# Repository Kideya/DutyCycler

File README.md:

# DutyCycler
A  lightweight PWM light dimmer designed for smooth brightness control. Tame your LEDs, shift the shades, and fade like a pro — whether you need a subtle glow or full party mode. Built for makers, hackers, and anyone who thinks "maximum brightness" is overrated.

- Generated with ChatGPT

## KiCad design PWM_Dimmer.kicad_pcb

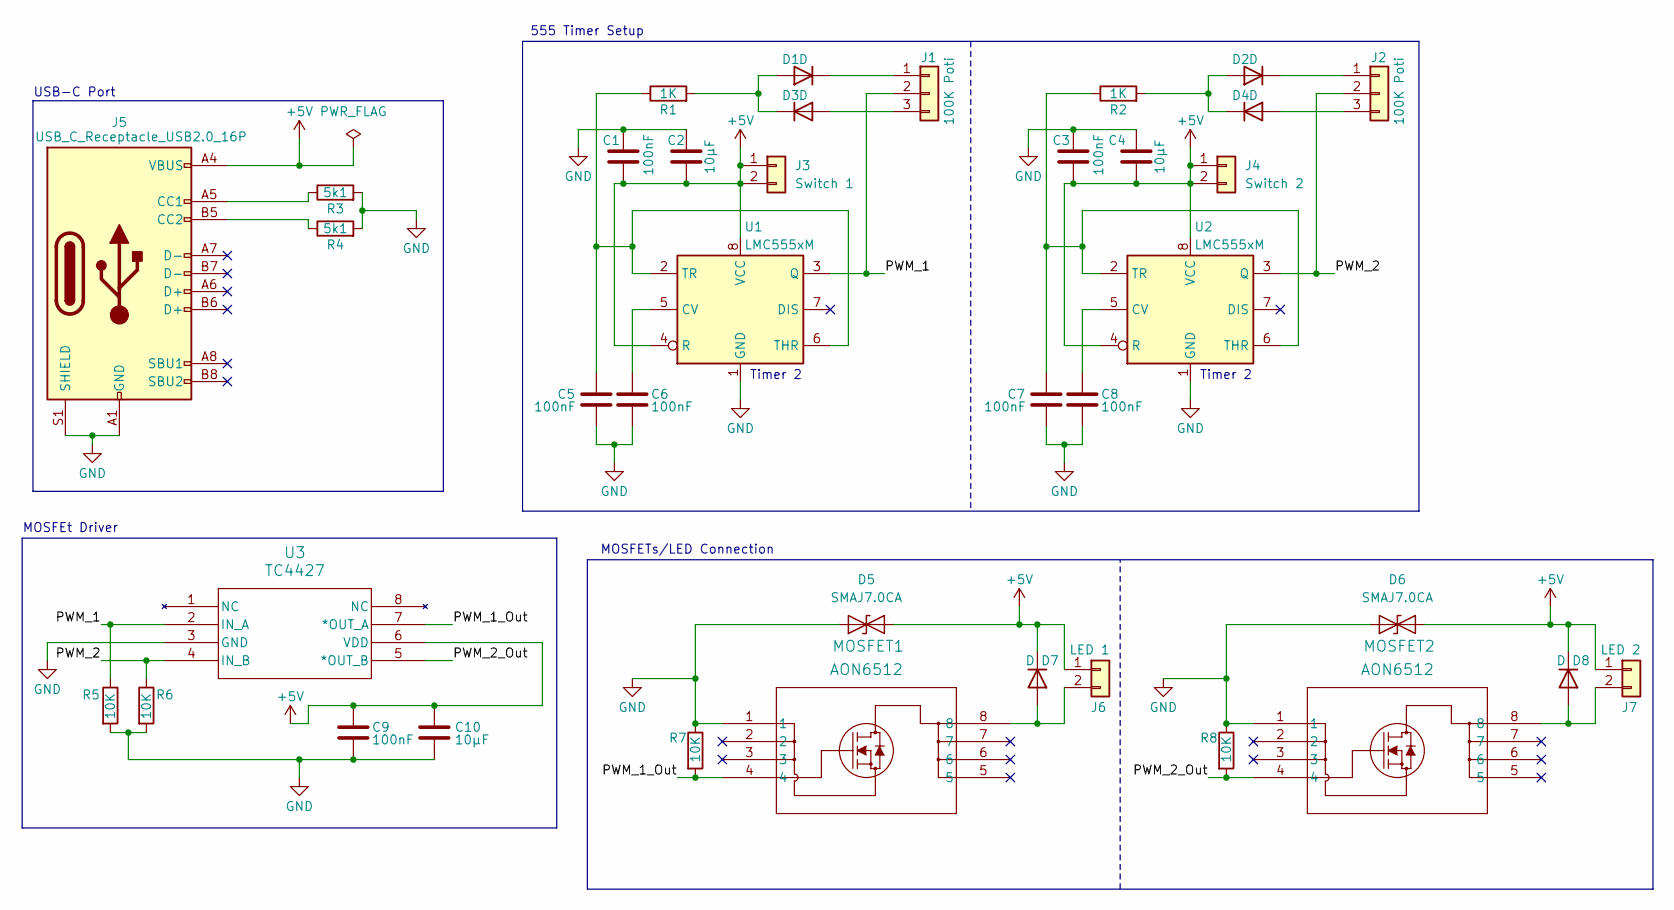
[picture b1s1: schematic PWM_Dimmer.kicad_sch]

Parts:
C1, C3, C5, C6, C7, C8, C9: 100nF; R_0603_1608Metric_Pad0.98x0.95mm_HandSolder
C2, C4, C10: 10µF; R_0603_1608Metric_Pad0.98x0.95mm_HandSolder
D1, D2, D3, D4, D7, D8: D; D_0603_1608Metric_Pad1.05x0.95mm_HandSolder
D5, D6: SMAJ7.0CA; D_SMB_Handsoldering
J1, J2: 100K Poti; PinHeader_1x03_P2.54mm_Vertical
J3: Switch 1; PinHeader_1x02_P2.54mm_Vertical
J4: Switch 2; PinHeader_1x02_P2.54mm_Vertical
J5: USB_C_Receptacle_USB2.0_16P; USB_C_Receptacle_Palconn_UTC16-G
J6: LED 1; Molex_PicoBlade_53047-0210_1x02_P1.25mm_Vertical
J7: LED 2; Molex_PicoBlade_53047-0210_1x02_P1.25mm_Vertical
MOSFET1, MOSFET2: AON6512; DFN5X6_8L_EP1_P_AOS
R1, R2: 1K; R_0603_1608Metric_Pad0.98x0.95mm_HandSolder
R3, R4: 5k1; R_0603_1608Metric_Pad0.98x0.95mm_HandSolder
R5, R6, R7, R8: 10K; R_0603_1608Metric_Pad0.98x0.95mm_HandSolder
U1, U2: LMC555xM; SOIC-8_3.9x4.9mm_P1.27mm
U3: TC4427; SOIC8-N_MC_MCH

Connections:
+5V: C1.2, C2.2, C3.2, C4.2, C9.1, C10.1, D5.1 (A1), D6.1 (A1), D7.1 (K), D8.1 (K), J3.1, J3.2, J4.1, J4.2, J5.A4 (VBUS), J5.A9 (VBUS), J5.B4 (VBUS), J5.B9 (VBUS), J6.1, J7.1, U1.4 (R), U1.8 (VCC), U2.4 (R), U2.8 (VCC), U3.6 (VDD)
/PWM_1: J1.2, R5.1, U1.3 (Q), U3.2 (IN_A)
/PWM_1_Out: MOSFET1.4, R7.2, U3.7 (*OUT_A)
/PWM_2: J2.2, R6.1, U2.3 (Q), U3.4 (IN_B)
/PWM_2_Out: MOSFET2.4, R8.2, U3.5 (*OUT_B)
GND: C1.1, C2.1, C3.1, C4.1, C5.2, C6.2, C7.2, C8.2, C9.2, C10.2, D5.2 (A2), D6.2 (A2), J5.A1 (GND), J5.A12 (GND), J5.B1 (GND), J5.B12 (GND), J5.S1 (SHIELD), MOSFET1.1, MOSFET2.1, R3.2, R4.2, R5.2, R6.2, R7.1, R8.1, U1.1 (GND), U2.1 (GND), U3.3 (GND)
unnamed: D1.2 (A), D3.1 (K), R1.2
unnamed: D1.1 (K), J1.1
unnamed: D2.2 (A), D4.1 (K), R2.2
unnamed: D2.1 (K), J2.1
unnamed: D3.2 (A), J1.3
unnamed: D4.2 (A), J2.3
unnamed: D7.2 (A), J6.2, MOSFET1.8
unnamed: D8.2 (A), J7.2, MOSFET2.8
unnamed: J5.A5 (CC1), R3.1
unnamed: J5.B5 (CC2), R4.1
unnamed: C6.1, U1.5 (CV)
unnamed: C5.1, R1.1, U1.2 (TR), U1.6 (THR)
unnamed: C8.1, U2.5 (CV)
unnamed: C7.1, R2.1, U2.2 (TR), U2.6 (THR)

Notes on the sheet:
555 Timer Setup
MOSFEt Driver
USB-C Port
Timer 2
MOSFETs/LED Connection

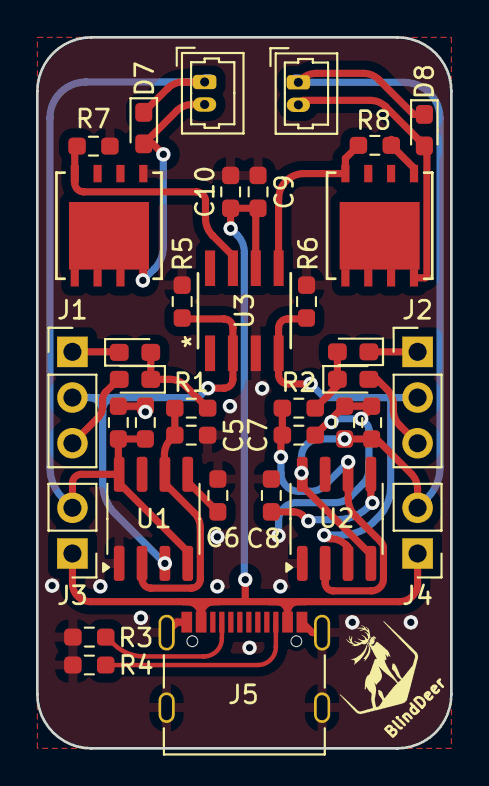
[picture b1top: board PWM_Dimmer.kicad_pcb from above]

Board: 2 copper layers, 23.0 x 39.5 mm, 36 parts (0 on the bottom side), 20 nets.

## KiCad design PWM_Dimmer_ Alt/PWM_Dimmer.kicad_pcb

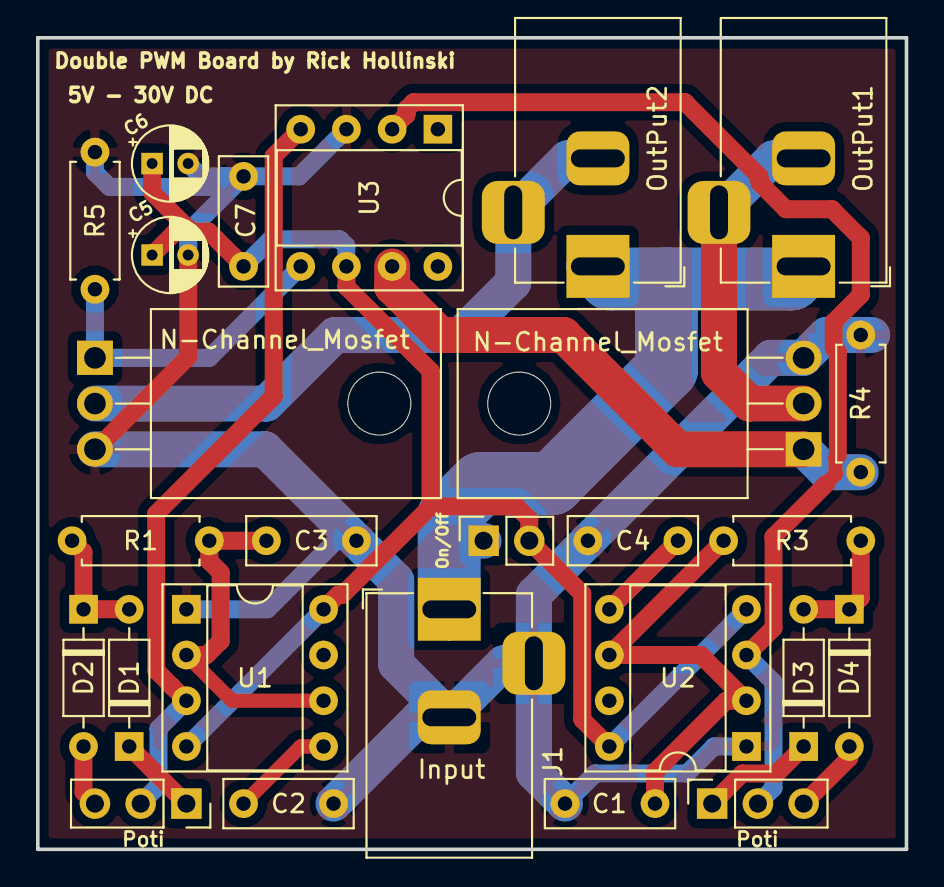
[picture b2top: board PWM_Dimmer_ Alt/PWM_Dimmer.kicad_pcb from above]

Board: 2 copper layers, 48.3 x 45.1 mm, 26 parts (0 on the bottom side), 19 nets.

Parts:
C1, C2, C3, C4, C7: 100n; C_Disc_D7.0mm_W2.5mm_P5.00mm
C5, C6: 10µ; CP_Radial_D4.0mm_P2.00mm
D1, D2, D3, D4: D; D_DO-35_SOD27_P7.62mm_Horizontal
J1: Input; BarrelJack_Horizontal
J2, J3: Poti; PinSocket_1x03_P2.54mm_Vertical
J4: OutPut1; BarrelJack_Horizontal
J5: OutPut2; BarrelJack_Horizontal
J6: On/Off; PinSocket_1x02_P2.54mm_Vertical
Q2, Q3: N-Channel_Mosfet; TO-220F-3_Horizontal_TabDown
R1, R3, R4, R5: 10K; R_Axial_DIN0207_L6.3mm_D2.5mm_P7.62mm_Horizontal
U1, U2: LMC555xN; DIP-8_W7.62mm_Socket
U3: TC4426CPA; DIP-8_W7.62mm_Socket

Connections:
+12V: J1.1, J4.1, J5.1, J6.1
GND: C1.2, C2.2, C3.2, C4.2, C5.2, C6.2, C7.2, J1.2, J1.3, Q2.3, Q3.3, R4.2, R5.2, U1.1, U2.1, U3.3
unnamed: C1.1, R3.2, U2.2, U2.6
unnamed: C2.1, U1.5
unnamed: C3.1, R1.2, U1.2, U1.6
unnamed: C4.1, U2.5
unnamed: D1.1, J2.1
unnamed: D1.2, D2.1, R1.1
unnamed: D2.2, J2.3
unnamed: D3.1, J3.1
unnamed: D3.2, D4.1, R3.1
unnamed: D4.2, J3.3
unnamed: J4.2, J4.3, Q2.2
unnamed: J5.2, J5.3, Q3.2
PWM_P_1: Q2.1, R4.1, U3.7
PWM_P_2: Q3.1, R5.1, U3.5
PWM_S_1: J3.2, U2.3, U3.2
PWM_S_2: J2.2, U1.3, U3.4
VCC: C5.1, C6.1, C7.1, J6.2, U1.4, U1.8, U2.4, U2.8, U3.6

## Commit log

2025-04-27 Added reference files
2025-04-28 Added schematic and first Layout
2025-04-28 Fixed Power line for LED-Strips and MOSFET driver, added Logo an Name
2025-04-28 changed readme fixed Name added ChatGPT note
